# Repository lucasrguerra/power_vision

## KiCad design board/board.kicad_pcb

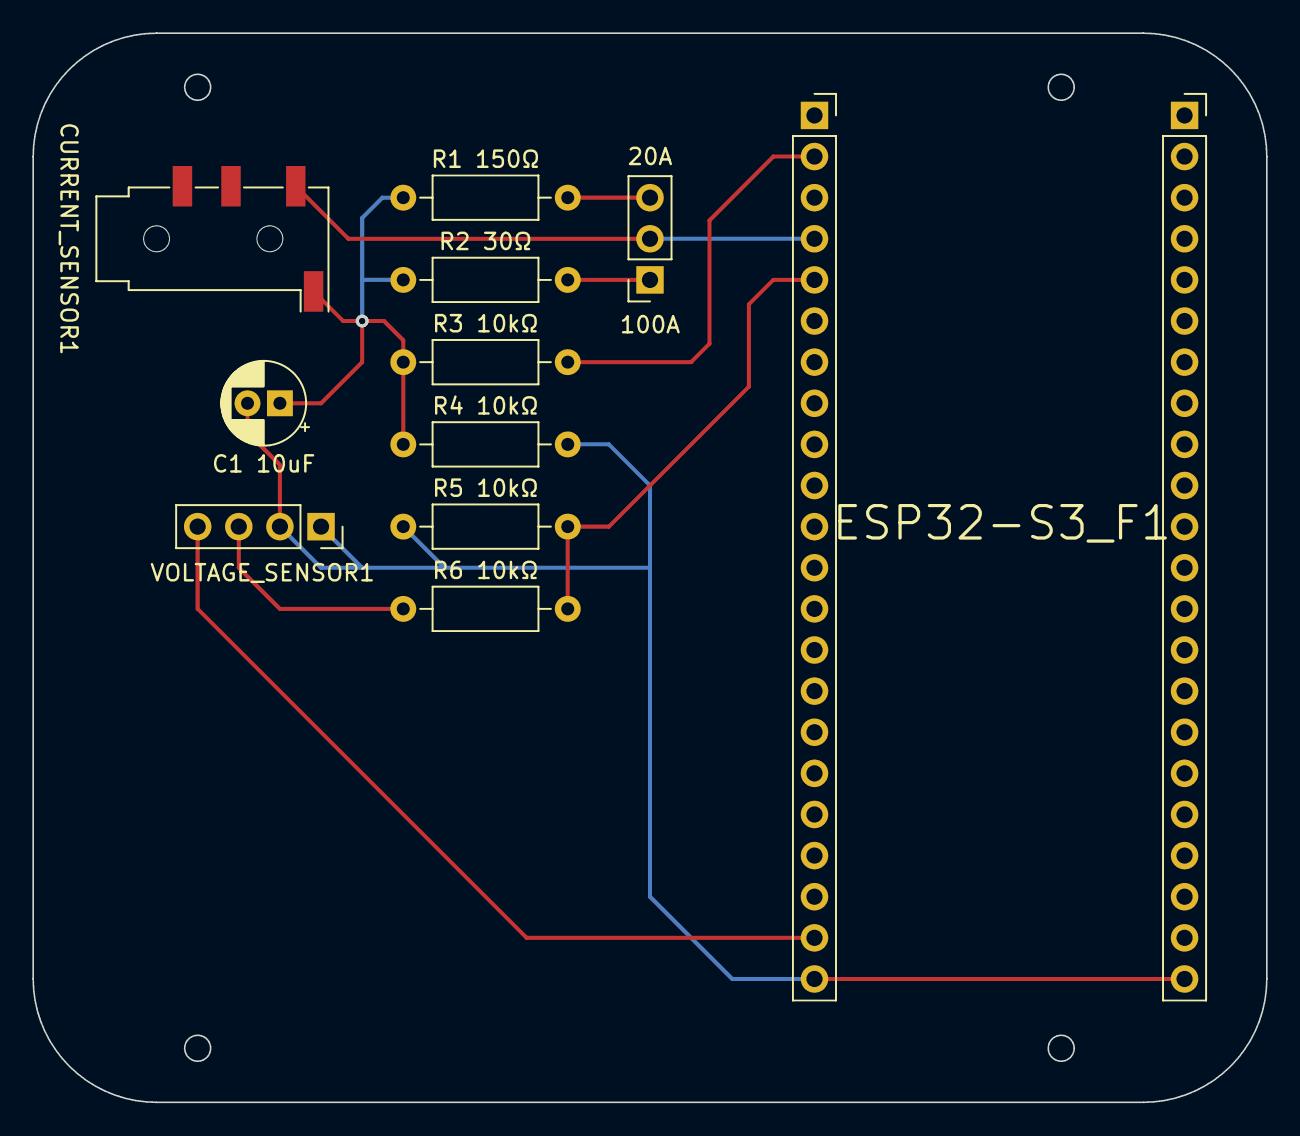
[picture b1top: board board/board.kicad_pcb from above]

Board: 2 copper layers, 76.2 x 66.0 mm, 12 parts (0 on the bottom side), 9 nets.

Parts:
100A: SW_Push_SPDT; PinSocket_1x03_P2.54mm_Vertical
C1 10uF: 10uF; CP_Radial_D5.0mm_P2.00mm
CURRENT_SENSOR1: AudioJack3; Jack_3.5mm_KoreanHropartsElec_PJ-320D-4A_Horizontal
ESP32-S3_B1, ESP32-S3_F1: Conn_01x22_Socket; PinSocket_1x22_P2.54mm_Vertical
R1 150Ω: 150; R_Axial_DIN0207_L6.3mm_D2.5mm_P10.16mm_Horizontal
R2 30Ω: 30; R_Axial_DIN0207_L6.3mm_D2.5mm_P10.16mm_Horizontal
R3 10kΩ, R4 10kΩ, R5 10kΩ, R6 10kΩ: 10k; R_Axial_DIN0207_L6.3mm_D2.5mm_P10.16mm_Horizontal
VOLTAGE_SENSOR1: Conn_01x04_Socket; PinSocket_1x04_P2.54mm_Vertical

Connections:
+3.3V: ESP32-S3_F1.1, ESP32-S3_F1.2, R3 10kΩ.2
C_SENSOR_ADC: 100A.2 (B), CURRENT_SENSOR1.T, ESP32-S3_F1.4
C_SENSOR_CONTROL: C1 10uF.1, CURRENT_SENSOR1.S, R1 150Ω.1, R2 30Ω.1, R3 10kΩ.1, R4 10kΩ.1
GND: C1 10uF.2, ESP32-S3_B1.21, ESP32-S3_B1.22, ESP32-S3_F1.22, R4 10kΩ.2, R5 10kΩ.1, VOLTAGE_SENSOR1.1, VOLTAGE_SENSOR1.2
unnamed: ESP32-S3_F1.5, R5 10kΩ.2, R6 10kΩ.2
SCALE-100A: 100A.1 (A), R2 30Ω.2
SCALE_20A: 100A.3 (C), R1 150Ω.2
VCC: ESP32-S3_F1.21, VOLTAGE_SENSOR1.4
V_SENSOR: R6 10kΩ.1, VOLTAGE_SENSOR1.3

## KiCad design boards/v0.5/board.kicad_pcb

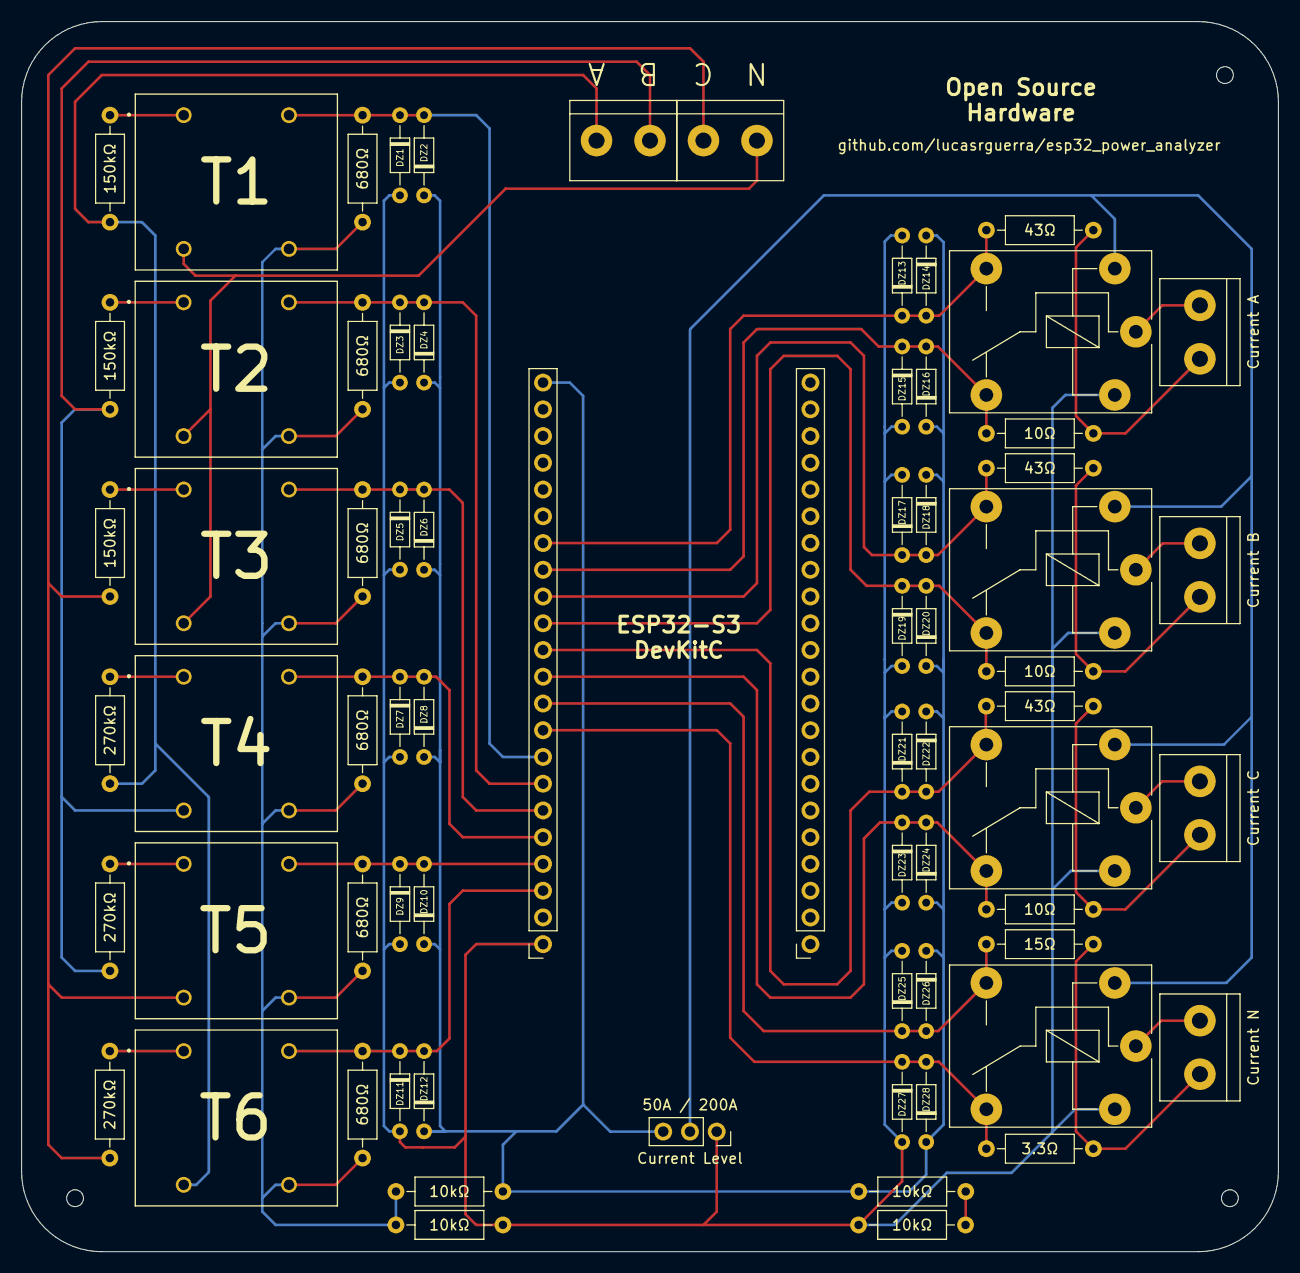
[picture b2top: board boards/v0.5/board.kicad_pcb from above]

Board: 2 copper layers, 119.4 x 116.8 mm, 71 parts (0 on the bottom side), 33 nets.

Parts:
B  A: Screw_Terminal_01x02; TerminalBlock_bornier-2_P5.08mm
Current A: Screw_Terminal_01x02; TerminalBlock_bornier-2_P5.08mm
Current B: Screw_Terminal_01x02; TerminalBlock_bornier-2_P5.08mm
Current C: Screw_Terminal_01x02; TerminalBlock_bornier-2_P5.08mm
Current Level: 50A / 200A; PinSocket_1x03_P2.54mm_Vertical
Current N: Screw_Terminal_01x02; TerminalBlock_bornier-2_P5.08mm
DZ1, DZ2, DZ3, DZ4, DZ5, DZ6, DZ7, DZ8, DZ9, DZ10, DZ11, DZ12, DZ13, DZ14, DZ15, DZ16, DZ17, DZ18, DZ19, DZ20, DZ21, DZ22, DZ23, DZ24, DZ25, DZ26, DZ27, DZ28: 3.3v; D_DO-34_SOD68_P7.62mm_Horizontal
ESP32-S3_BACK1, ESP32-S3_FRONT1: Conn_01x22_Socket; PinSocket_1x22_P2.54mm_Vertical
K1, K2, K3, K4: FINDER-36.11; Relay_SPDT_Finder_36.11
N  C: Screw_Terminal_01x02; TerminalBlock_bornier-2_P5.08mm
R1, R3, R5: 150kΩ; R_Axial_DIN0207_L6.3mm_D2.5mm_P10.16mm_Horizontal
R2, R4, R6, R8, R10, R12: 680Ω; R_Axial_DIN0207_L6.3mm_D2.5mm_P10.16mm_Horizontal
R7, R9, R11: 270kΩ; R_Axial_DIN0207_L6.3mm_D2.5mm_P10.16mm_Horizontal
R13, R15, R17: 43Ω; R_Axial_DIN0207_L6.3mm_D2.5mm_P10.16mm_Horizontal
R14, R16, R18: 10Ω; R_Axial_DIN0207_L6.3mm_D2.5mm_P10.16mm_Horizontal
R19: 15Ω; R_Axial_DIN0207_L6.3mm_D2.5mm_P10.16mm_Horizontal
R20: 3.3Ω; R_Axial_DIN0207_L6.3mm_D2.5mm_P10.16mm_Horizontal
R21, R22, R23, R24: 10kΩ; R_Axial_DIN0207_L6.3mm_D2.5mm_P10.16mm_Horizontal
T1, T2, T3, T4, T5, T6: ZMPT101B; XFMR_ZMPT101B

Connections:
A_Current: Current A.2, K1.11
B_Current: Current B.2, K2.11
C_Current: Current C.2, K3.11
Current_A_50A: DZ13.1 (K), DZ14.2 (A), ESP32-S3_FRONT1.16, K1.14, R13.2
Current_A_200A: DZ15.1 (K), DZ16.2 (A), ESP32-S3_FRONT1.15, K1.12, R14.1
Current_B_50A: DZ17.1 (K), DZ18.2 (A), ESP32-S3_FRONT1.14, K2.14, R15.2
Current_B_200A: DZ19.1 (K), DZ20.2 (A), ESP32-S3_FRONT1.13, K2.12, R16.1
Current_C_50A: DZ21.1 (K), DZ22.2 (A), ESP32-S3_FRONT1.12, K3.14, R17.2
Current_C_200A: DZ23.1 (K), DZ24.2 (A), ESP32-S3_FRONT1.11, K3.12, R18.1
Current_N_150A: DZ25.1 (K), DZ26.2 (A), ESP32-S3_FRONT1.10, K4.14, R19.2
Current_N_600A: DZ27.1 (K), DZ28.2 (A), ESP32-S3_FRONT1.9, K4.12, R20.1
GND: Current Level.1 (A), DZ1.2 (A), DZ3.2 (A), DZ5.2 (A), DZ7.2 (A), DZ9.2 (A), DZ11.2 (A), DZ13.2 (A), DZ15.2 (A), DZ17.2 (A), DZ19.2 (A), DZ21.2 (A), DZ23.2 (A), DZ25.2 (A), DZ27.2 (A), ESP32-S3_FRONT1.1, K1.A2, K2.A2, K3.A2, K4.A2, R22.2, R24.1
Line_A: B A.2, R1.1, R7.1, T6.2
Line_AB_Load: R7.2, T4.1
Line_AB_Wave: DZ7.1 (K), DZ8.2 (A), ESP32-S3_FRONT1.5, R8.2, T4.4
Line_AC_Load: R11.2, T6.1
Line_AC_Wave: DZ11.1 (K), DZ12.2 (A), ESP32-S3_FRONT1.3, R12.2, T6.4
Line_A_Load: R1.2, T1.1
Line_A_Wave: DZ1.1 (K), DZ2.2 (A), ESP32-S3_FRONT1.8, R2.2, T1.4
Line_B: B A.1, R3.1, R9.1, T4.2
Line_BC_Load: R9.2, T5.1
Line_BC_Wave: DZ9.1 (K), DZ10.2 (A), ESP32-S3_FRONT1.4, R10.2, T5.4
Line_B_Load: R3.2, T2.1
Line_B_Wave: DZ3.1 (K), DZ4.2 (A), ESP32-S3_FRONT1.7, R4.2, T2.4
Line_C: N C.2, R5.1, R11.1, T5.2
Line_C_Load: R5.2, T3.1
Line_C_Wave: DZ5.1 (K), DZ6.2 (A), ESP32-S3_FRONT1.6, R6.2, T3.4
N_Current: Current N.2, K4.11
Neutral: N C.1, T1.2, T2.2, T3.2
Select_Current: Current Level.2 (B), K1.A1, K2.A1, K3.A1, K4.A1
VCC: Current Level.3 (C), DZ2.1 (K), DZ4.1 (K), DZ6.1 (K), DZ8.1 (K), DZ10.1 (K), DZ12.1 (K), DZ14.1 (K), DZ16.1 (K), DZ18.1 (K), DZ20.1 (K), DZ22.1 (K), DZ24.1 (K), DZ26.1 (K), DZ28.1 (K), ESP32-S3_FRONT1.22, R21.2, R23.1
V_Ref_C: Current A.1, Current B.1, Current C.1, Current N.1, R13.1, R14.2, R15.1, R16.2, R17.1, R18.2, R19.1, R20.2, R23.2, R24.2
V_Ref_V: R2.1, R4.1, R6.1, R8.1, R10.1, R12.1, R21.1, R22.1, T1.3, T2.3, T3.3, T4.3, T5.3, T6.3

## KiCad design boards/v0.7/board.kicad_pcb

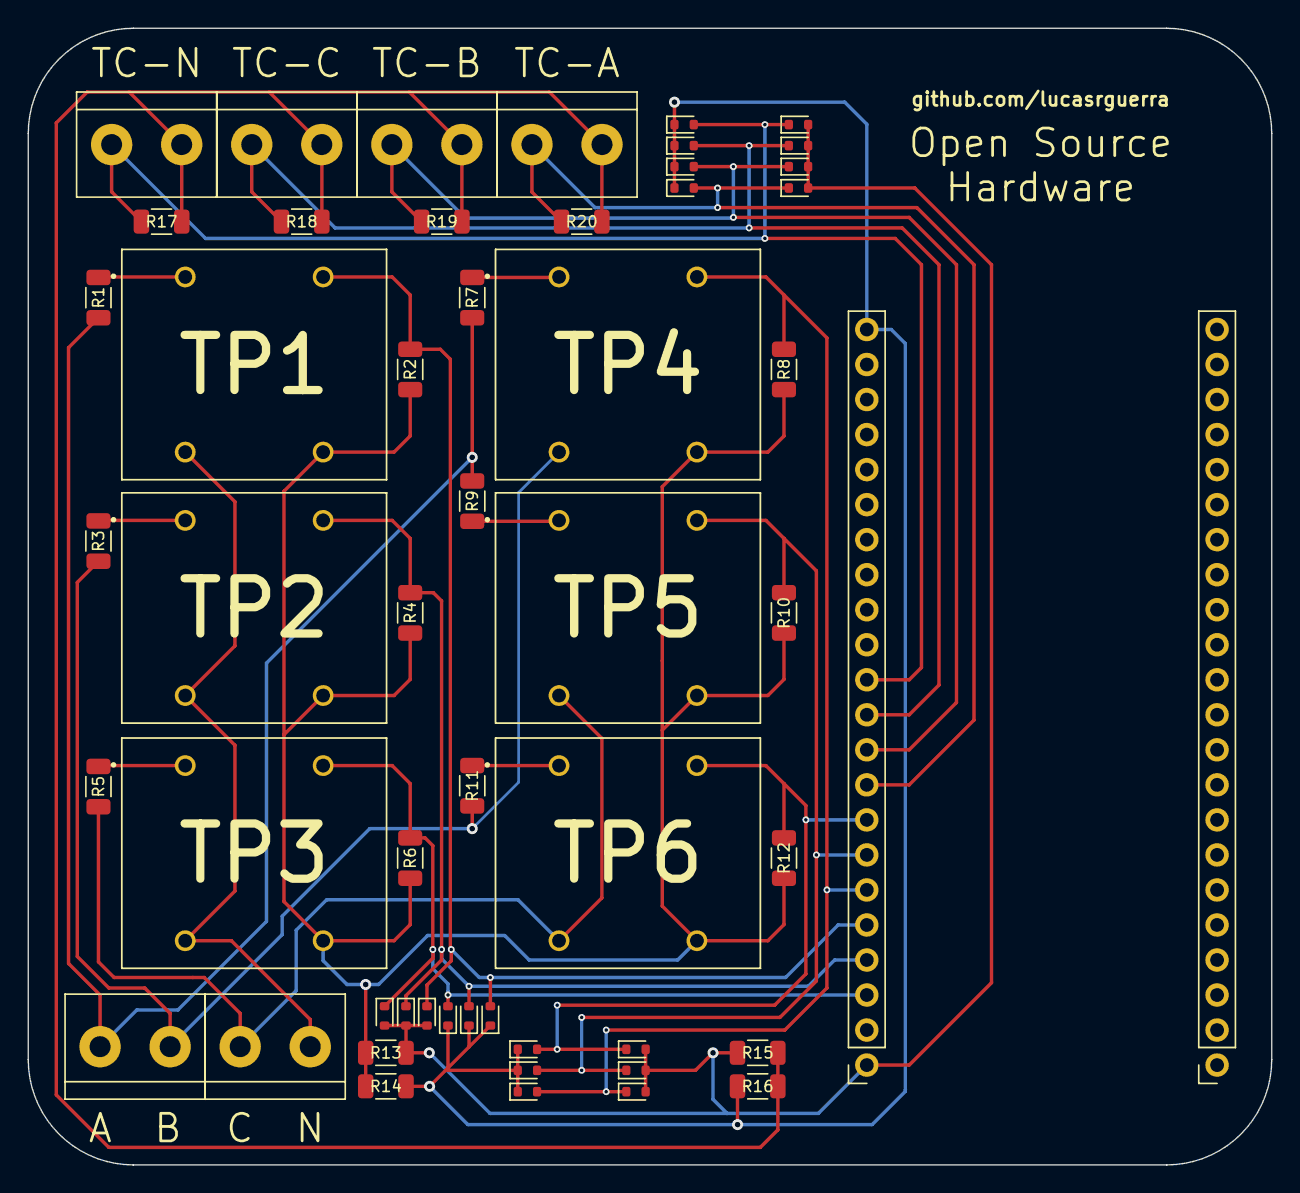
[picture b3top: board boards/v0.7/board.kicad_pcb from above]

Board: 2 copper layers, 90.2 x 82.4 mm, 54 parts (0 on the bottom side), 24 nets.

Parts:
DZ1, DZ1#2, DZ3, DZ4, DZ5, DZ6, DZ7, DZ8, DZ9, DZ10, DZ11, DZ12, DZ13, DZ14, DZ15, DZ15#2, DZ17, DZ18, DZ19, DZ20: D_SOD-523
ESP32-S3_BACK1, ESP32-S3_FRONT1: Conn_01x22_Socket; PinSocket_1x22_P2.54mm_Vertical
R1, R2, R3, R4, R5, R6, R7, R8, R9, R10, R11, R12, R13, R14, R15, R16, R17, R18, R19, R20: R_1206 ±0.1%; R_1206_3216Metric
ST1, ST2, ST3, ST4, ST5, ST6: WJ127-5.0-2P; TerminalBlock_bornier-2_P5.08mm
TP1, TP2, TP3, TP4, TP5, TP6: ZMPT101B; XFMR_ZMPT101B

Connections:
AB_Voltage_Load: R7.1, TP4.1
AB_Wave: DZ9.2, DZ12.1, ESP32-S3_FRONT1.6, R8.2, TP4.4
AC_Voltage_Load: R9.2, TP5.1
AC_Wave: DZ8.2, DZ11.1, ESP32-S3_FRONT1.7, R10.2, TP5.4
A_Current_Wave: DZ13.2, DZ17.1, ESP32-S3_FRONT1.9, R20.2, ST3.2
A_Voltage: R1.2, R7.2, R9.1, ST1.1
A_Voltage_Load: R1.1, TP1.1
A_Wave: DZ3.1, DZ6.2, ESP32-S3_FRONT1.5, R2.2, TP1.4
BC_Voltage_Load: R11.1, TP6.1
BC_Wave: DZ7.2, DZ10.1, ESP32-S3_FRONT1.8, R12.2, TP6.4
B_Current_Wave: DZ14.2, DZ18.1, ESP32-S3_FRONT1.10, R19.2, ST4.2
B_Voltage: R3.2, R11.2, ST1.2, TP4.2
B_Voltage_Load: R3.1, TP2.1
B_Wave: DZ1.1, DZ5.2, ESP32-S3_FRONT1.4, R4.2, TP2.4
C_Current_Wave: DZ15.2, DZ19.1, ESP32-S3_FRONT1.11, R18.2, ST5.2
C_Voltage: R5.1, ST2.1, TP5.2, TP6.2
C_Voltage_Load: R5.2, TP3.1
C_Wave: DZ1#2.1, DZ4.2, ESP32-S3_FRONT1.3, R6.2, TP3.4
GND: DZ1.2, DZ1#2.2, DZ3.2, DZ10.2, DZ11.2, DZ12.2, DZ17.2, DZ18.2, DZ19.2, DZ20.2, ESP32-S3_FRONT1.1, R13.1, R15.1
N_Current_Wave: DZ15#2.2, DZ20.1, ESP32-S3_FRONT1.12, R17.1, ST6.2
N_Voltage: ST2.2, TP1.2, TP2.2, TP3.2
VCC: DZ4.1, DZ5.1, DZ6.1, DZ7.1, DZ8.1, DZ9.1, DZ13.1, DZ14.1, DZ15.1, DZ15#2.1, ESP32-S3_FRONT1.22, R14.1, R16.1
V_Ref_Current: R15.2, R16.2, R17.2, R18.1, R19.1, R20.1, ST3.1, ST4.1, ST5.1, ST6.1
V_Ref_Voltage: R2.1, R4.1, R6.1, R8.1, R10.1, R12.1, R13.2, R14.2, TP1.3, TP2.3, TP3.3, TP4.3, TP5.3, TP6.3
